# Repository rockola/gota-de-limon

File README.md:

gota-de-limon
================

Lumpy's Lemon Drop

* v0.1: initial revision, unverified

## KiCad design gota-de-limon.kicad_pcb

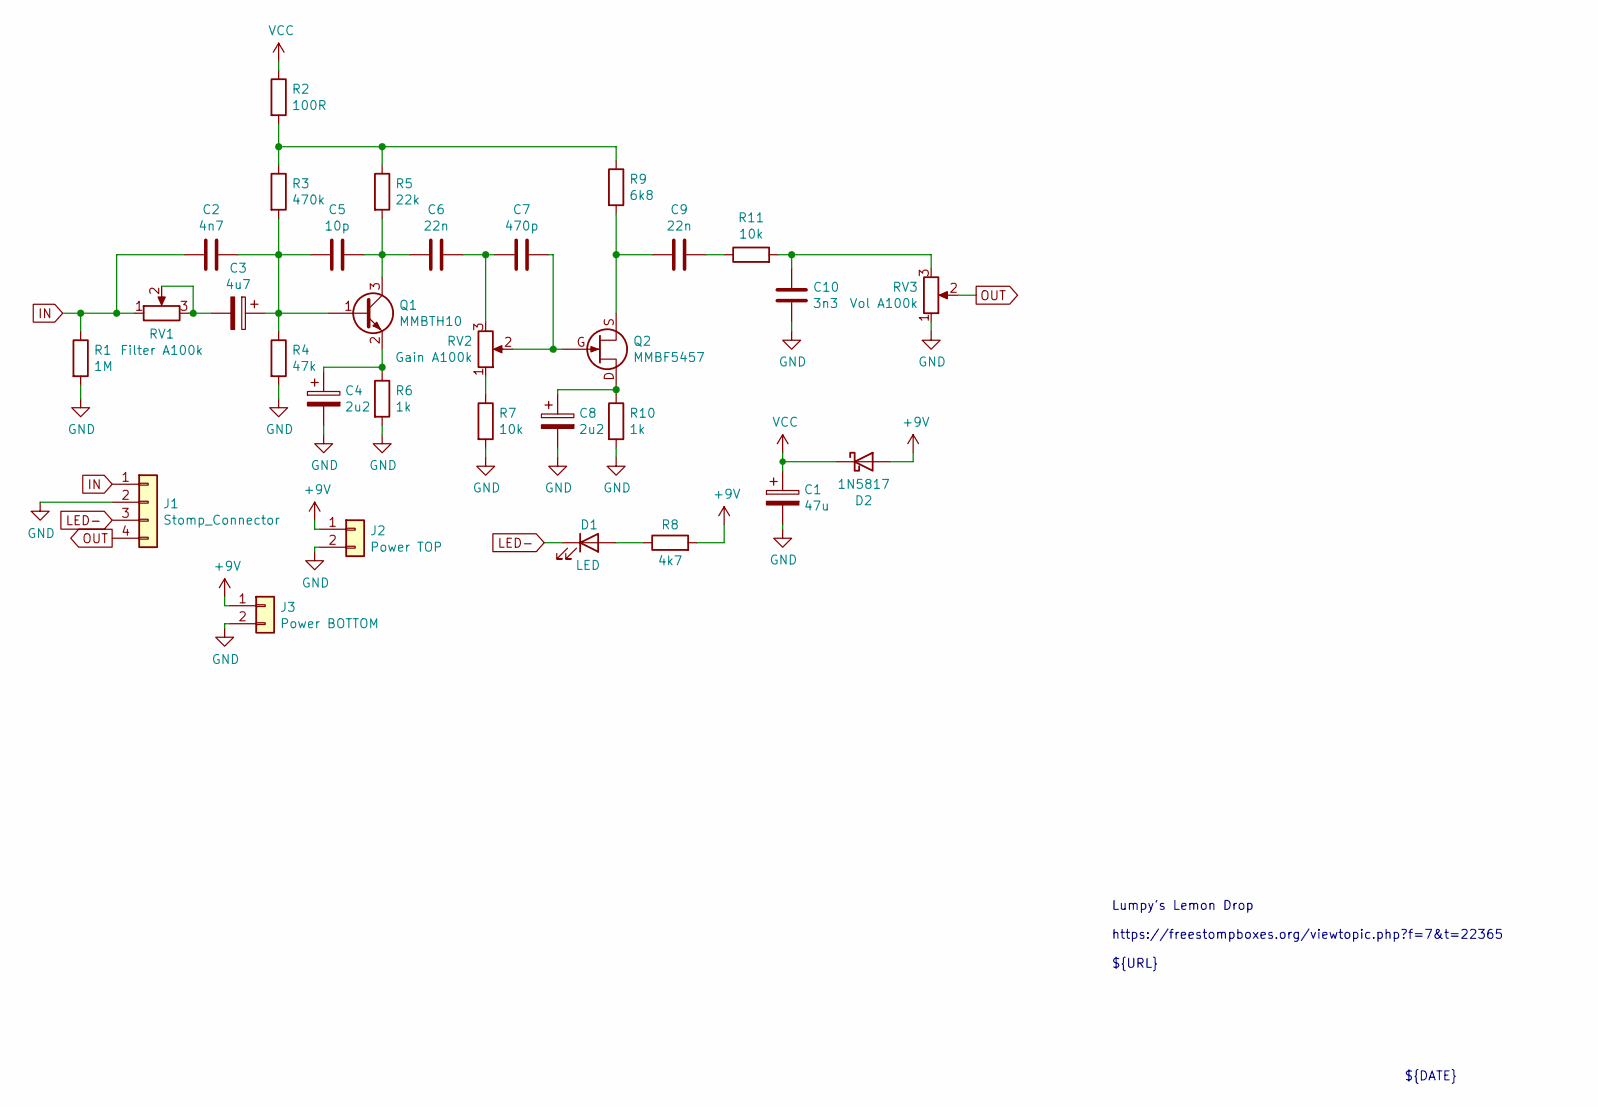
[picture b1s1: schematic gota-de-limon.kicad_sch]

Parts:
C1: 47u; CP_D5.0_P2.50
C2: 4n7; C_Box_7.2_2.5
C3: 4u7; CP_D5.0_P2.50
C4, C8: 2u2; CP_D5.0_P2.50
C5: 10p; C_Box_7.2_2.5
C6, C9: 22n; C_Box_7.2_2.5
C7: 470p; C_Box_7.2_2.5
C10: 3n3; C_Box_7.2_2.5
D1: LED; LED_D3.0mm
D2: 1N5817; D_DO-41_SOD81_P7.62mm_Horizontal
J1: Stomp_Connector; Stomp_4pin
J2: Power TOP; Power_Header_2pin
J3: Power BOTTOM; Power_Header_2pin
Q1: MMBTH10; SOT-23
Q2: MMBF5457; SOT-23_NJFET_DSG_Handsoldering
R1: 1M; R_DIN0207
R2: 100R; R_DIN0207
R3: 470k; R_DIN0207
R4: 47k; R_DIN0207
R5: 22k; R_DIN0207
R6, R10: 1k; R_DIN0207
R7, R11: 10k; R_DIN0207
R8: 4k7; R_DIN0207
R9: 6k8; R_DIN0207
RV1: Filter A100k; 16mm_BoardMount
RV2: Gain A100k; 16mm_BoardMount
RV3: Vol A100k; 16mm_BoardMount

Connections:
+9V: D2.2 (A), J2.1 (PWR), J3.1 (PWR), R8.2
GND: C1.2, C4.2, C8.2, C10.2, J1.2 (GND), J2.2 (GND), J3.2 (GND), R1.2, R4.2, R6.2, R7.2, R10.2, RV3.1
IN: C2.1, J1.1 (IN), R1.1, RV1.1
LED-: D1.1 (K), J1.3 (SW)
unnamed: C2.2, C3.1, C5.1, Q1.1 (B), R3.2, R4.1
unnamed: C3.2, RV1.2, RV1.3
unnamed: C4.1, Q1.2 (E), R6.1
unnamed: C5.2, C6.1, Q1.3 (C), R5.2
unnamed: C6.2, C7.1, RV2.3
unnamed: C7.2, Q2.G, RV2.2
unnamed: C8.1, Q2.D, R10.1
unnamed: C9.1, Q2.S, R9.2
unnamed: C9.2, R11.1
unnamed: C10.1, R11.2, RV3.3
unnamed: D1.2 (A), R8.1
unnamed: R2.2, R3.1, R5.1, R9.1
unnamed: R7.1, RV2.1
OUT: J1.4 (OUT), RV3.2
VCC: C1.1, D2.1 (K), R2.1

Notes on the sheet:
${DATE}
${TITLE}
Lumpy's Lemon Drop https://freestompboxes.org/viewtopic.php?f=7&t=22365 ${URL}
${REVISION}

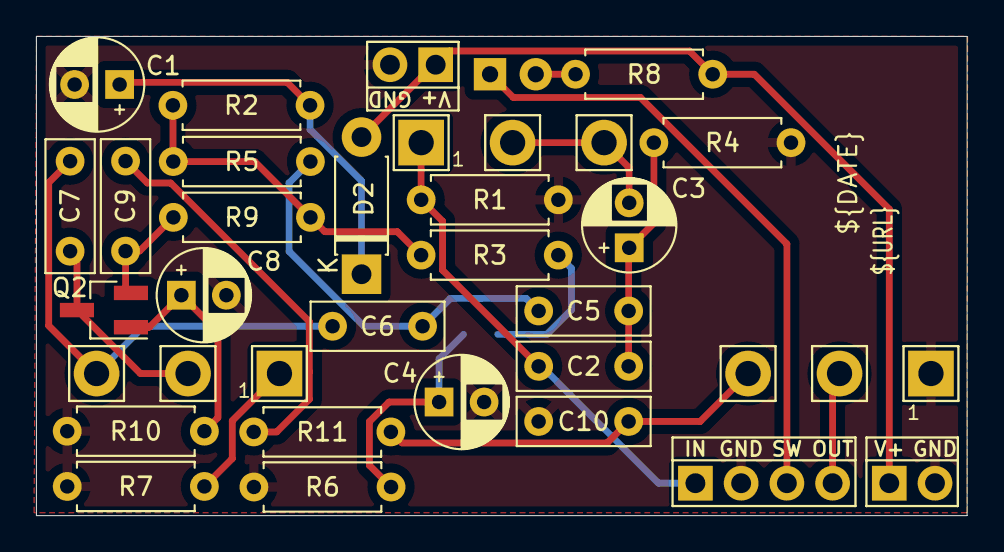
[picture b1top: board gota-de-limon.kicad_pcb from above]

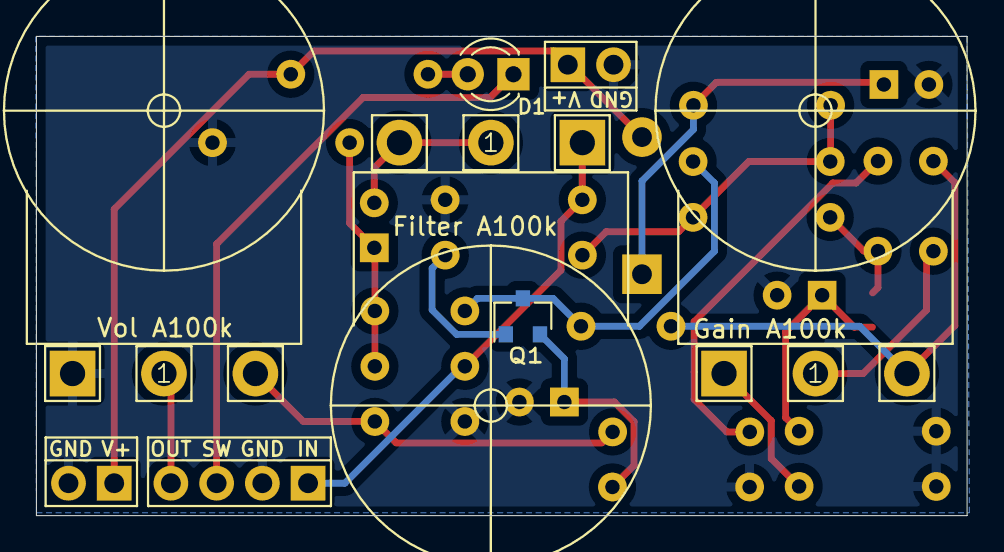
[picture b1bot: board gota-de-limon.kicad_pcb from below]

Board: 2 copper layers, 51.7 x 26.6 mm, 31 parts (2 on the bottom side), 19 nets.

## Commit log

2020-11-24 v0.1 initial
2021-03-25 updated to new kicad file format
2021-03-25 schematic, preview images
2021-03-25 initial README
2022-01-11 updated to KiCad 6.0
